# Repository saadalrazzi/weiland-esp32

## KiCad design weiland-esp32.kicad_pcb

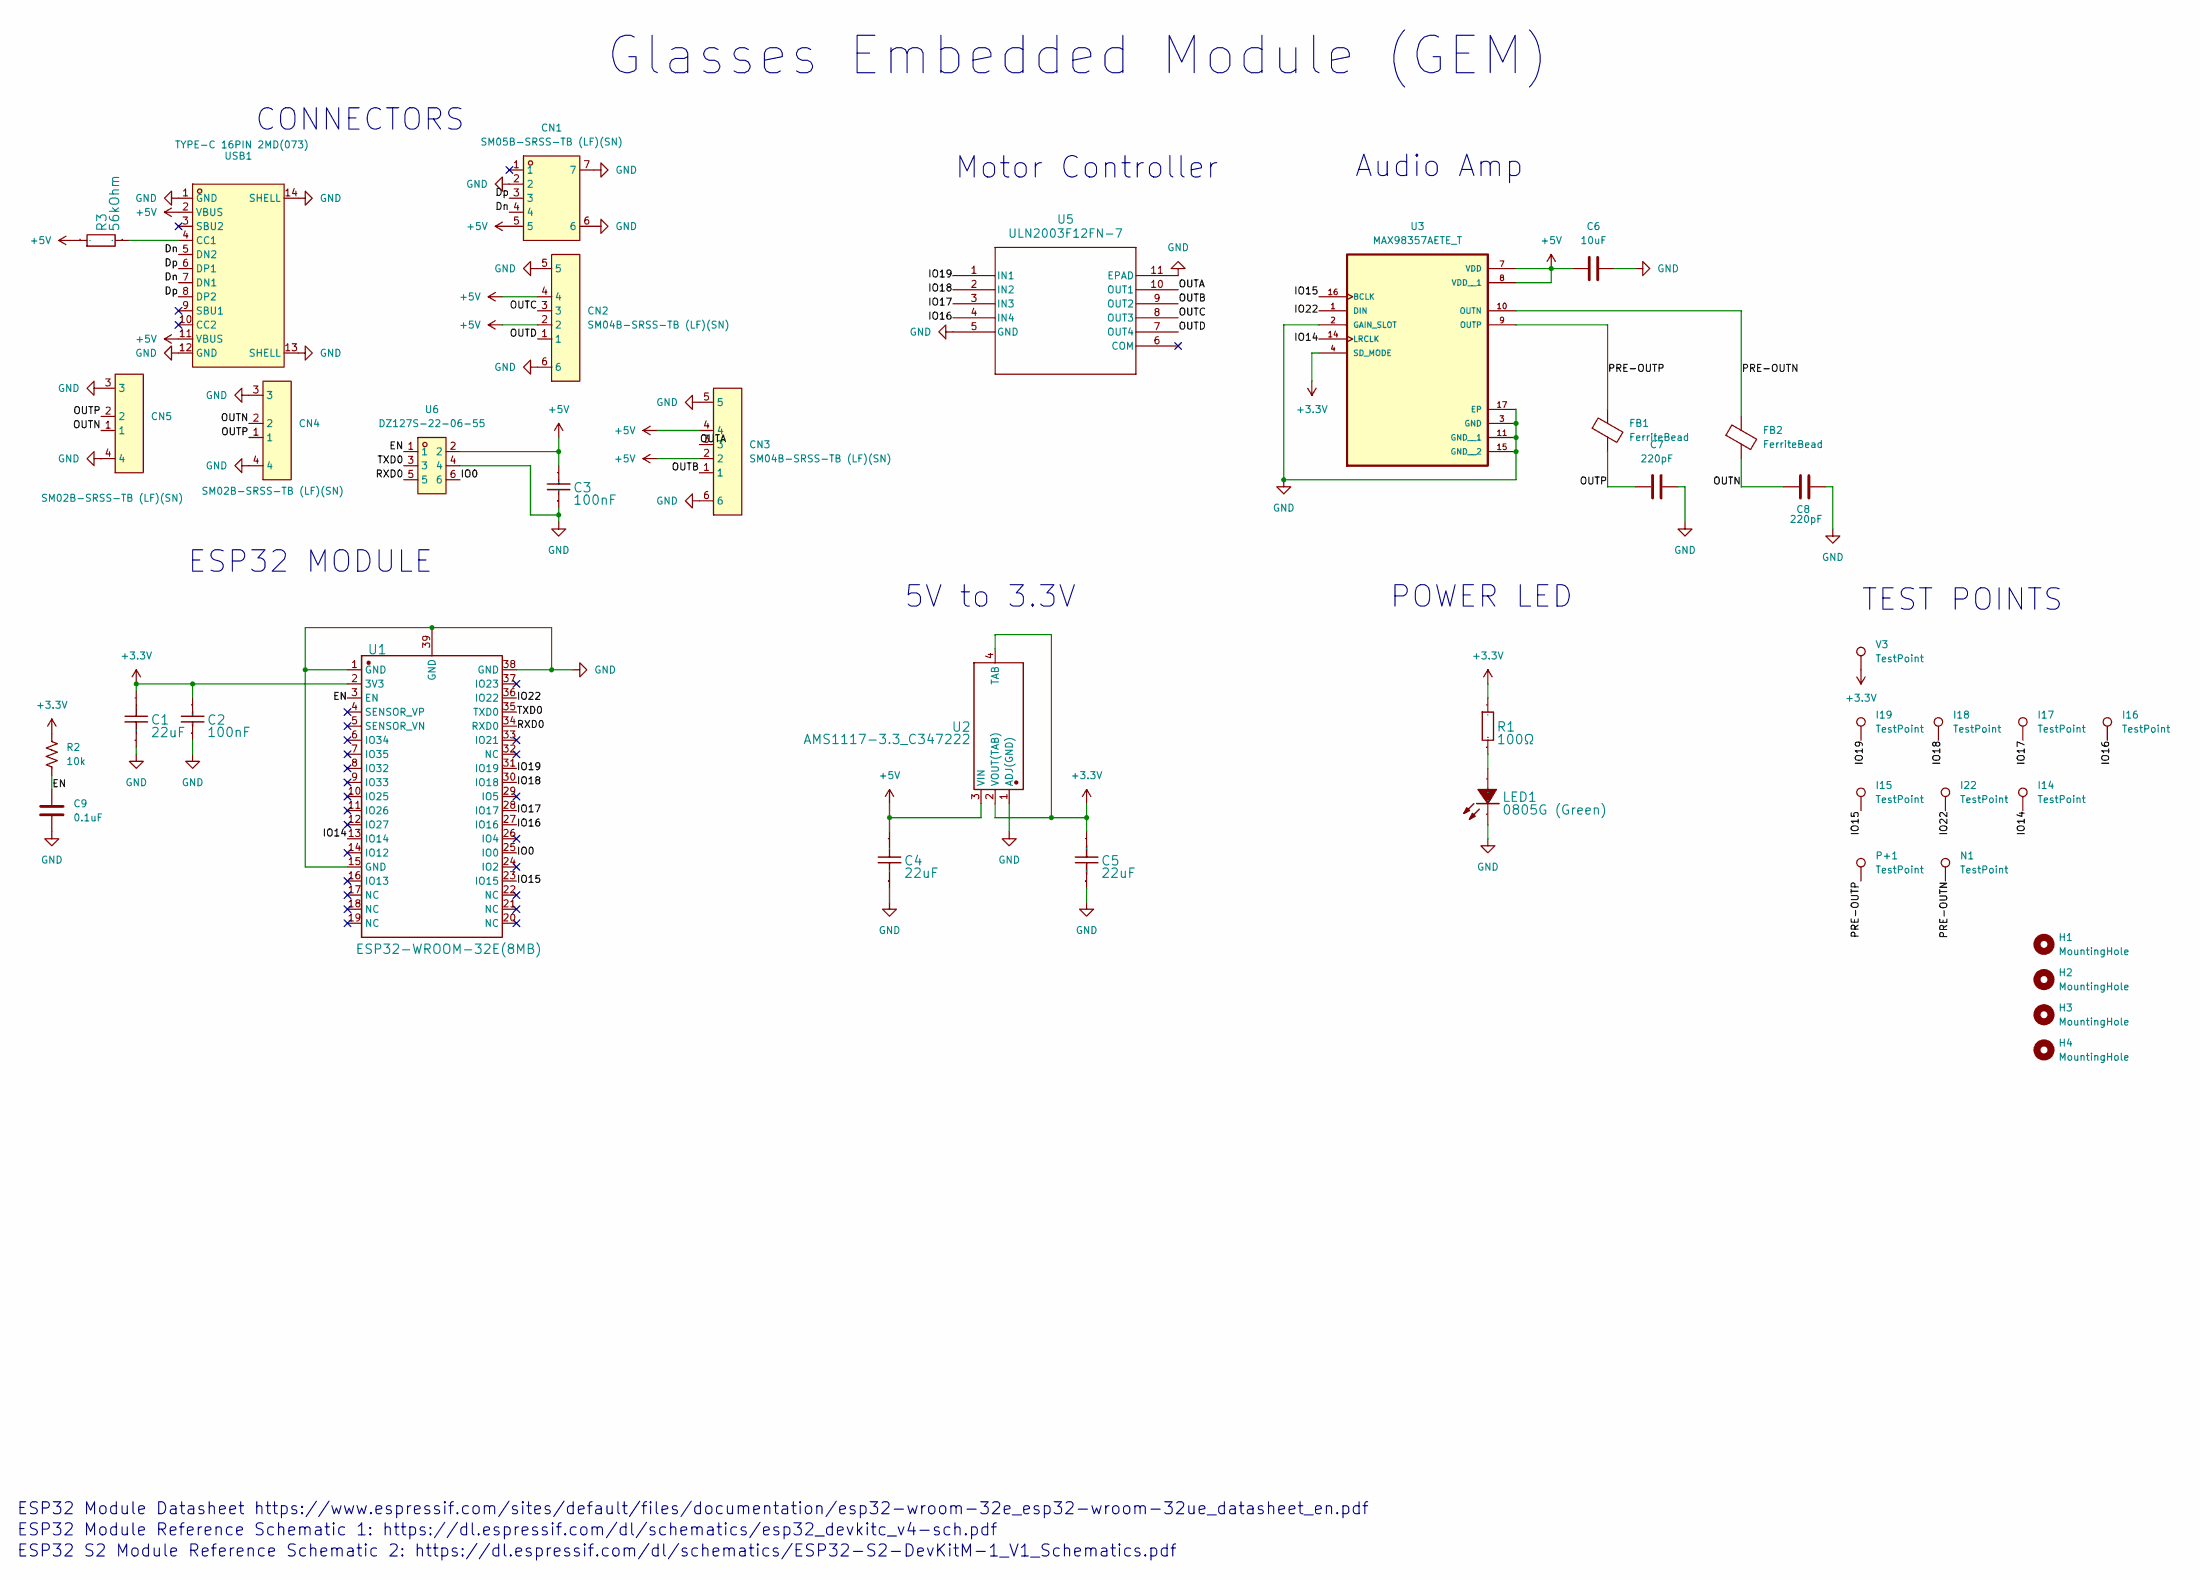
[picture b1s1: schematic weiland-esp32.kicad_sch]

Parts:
C1: 22uF; RESC1005X40N; Manufacturer Part CL21A226MAYNNNE
C2, C3: 100nF; CAPC1005X55N; Manufacturer Part CL05B104KO5NNNC
C4, C5: 22uF; RESC1005X40N; Manufacturer Part CL05A106MP5NUNC
C6: 10uF; RESC1005X40N
C7, C8: 220pF; RESC1005X40N
C9: 0.1uF; C_0402_1005Metric
CN1: SM05B-SRSS-TB (LF)(SN); CONN-SMD_SM05B-SRSS-TB-LF-SN; LCSC Part C136657
CN2, CN3: SM04B-SRSS-TB (LF)(SN); CONN-SMD_4P-P1.00_SM04B-SRSS-TB-LF-SN; LCSC Part C160404
CN4, CN5: SM02B-SRSS-TB (LF)(SN); CONN-SMD_2P-P1.00_SM02B-SRSS-TB-LF-SN; LCSC Part C160402
FB1, FB2: FerriteBead; 0402ferritebead
H1, H2, H3, H4: MountingHole; MountingHole_3.2mm_M3
I14, I15, I16, I17, I18, I19, I22: TestPoint; TestPoint_Pad_D1.0mm
LED1: 0805G (Green); LED_KP-1608SURCK; Manufacturer Part 0805G (Green)
N1: TestPoint; TestPoint_Pad_D1.0mm
P+1: TestPoint; TestPoint_Pad_D1.0mm
R1: 100Ω; RESC1005X40N; Manufacturer Part 0402WGF5101TCE
R2: 10k; R_0402_1005Metric
R3: 56kOhm; R_0402_1005Metric; Manufacturer Part 0402WGF5101TCE
U1: ESP32-WROOM-32E(8MB); ESP32-WROOM-32E; Manufacturer Part ESP32-WROOM-32E(8MB)
U2: AMS1117-3.3_C347222; SOT229P700X180-4N; Manufacturer Part AMS1117-3.3
U3: MAX98357AETE_T; QFN50P300X300X80-17N
U5: ULN2003F12FN-7; U-DFN3030-10_DIO
U6: DZ127S-22-06-55; HDR-SMD_6P-P1.27-V-M-R2-C3-S1.27-LS5.5-1; LCSC Part C5160759
USB1: TYPE-C 16PIN 2MD(073); USB-C-SMD_TYPE-C-6PIN-2MD-073; LCSC Part C2765186
V3: TestPoint; TestPoint_Pad_D1.0mm

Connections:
+3.3V: C1.2, C2.2, C5.2, R1.2, R2.1, U1.2 (3V3), U2.2 (VOUT(TAB)), U2.4 (TAB), U3.4 (SD_MODE), V3.1
+5V: C3.2, C4.2, C6.1, CN1.5, CN2.2, CN2.4, CN3.2, CN3.4, R3.2, U2.3 (VIN), U3.7 (VDD), U3.8 (VDD__1), U6.2, USB1.2 (VBUS), USB1.11 (VBUS)
/Dn: CN1.4, USB1.5 (DN2), USB1.7 (DN1)
/Dp: CN1.3, USB1.6 (DP1), USB1.8 (DP2)
/EN: C9.1, R2.2, U1.3 (EN), U6.1
/IO0: U1.25 (IO0), U6.6
/IO14: I14.1, U1.13 (IO14), U3.14 (LRCLK)
/IO15: I15.1, U1.23 (IO15), U3.16 (BCLK)
/IO16: I16.1, U1.27 (IO16), U5.4 (IN4)
/IO17: I17.1, U1.28 (IO17), U5.3 (IN3)
/IO18: I18.1, U1.30 (IO18), U5.2 (IN2)
/IO19: I19.1, U1.31 (IO19), U5.1 (IN1)
/IO22: I22.1, U1.36 (IO22), U3.1 (DIN)
/OUTA: CN3.3, U5.10 (OUT1)
/OUTB: CN3.1, U5.9 (OUT2)
/OUTC: CN2.3, U5.8 (OUT3)
/OUTD: CN2.1, U5.7 (OUT4)
/OUTN: C8.1, CN4.2, CN5.1, FB2.2
/OUTP: C7.1, CN4.1, CN5.2, FB1.2
/PRE-OUTN: FB2.1, N1.1, U3.10 (OUTN)
/PRE-OUTP: FB1.1, P+1.1, U3.9 (OUTP)
/RXD0: U1.34 (RXD0), U6.5
/TXD0: U1.35 (TXD0), U6.3
GND: C1.1, C2.1, C3.1, C4.1, C5.1, C6.2, C7.2, C8.2, C9.2, CN1.2, CN1.6, CN1.7, CN2.5, CN2.6, CN3.5, CN3.6, CN4.3, CN4.4, CN5.3, CN5.4, LED1.1 (K), U1.1 (GND), U1.15 (GND), U1.38 (GND), U1.39 (GND), U2.1 (ADJ(GND)), U3.2 (GAIN_SLOT), U3.3 (GND), U3.11 (GND__1), U3.15 (GND__2), U3.17 (EP), U5.5 (GND), U5.11 (EPAD), U6.4, USB1.1 (GND), USB1.12 (GND), USB1.13 (SHELL), USB1.14 (SHELL)
unnamed: LED1.2 (A), R1.1
unnamed: R3.1, USB1.4 (CC1)

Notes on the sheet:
POWER LED
Motor Controller
Glasses Embedded Module (GEM)
ESP32 Module Reference Schematic 1: https://dl.espressif.com/dl/schematics/esp32_devkitc_v4-sch.pdf
Audio Amp
TEST POINTS
ESP32 MODULE
CONNECTORS
ESP32 Module Datasheet https://www.espressif.com/sites/default/files/documentation/esp32-wroom-32e_esp32-wroom-32ue_datasheet_en.pdf
5V to 3.3V
ESP32 S2 Module Reference Schematic 2: https://dl.espressif.com/dl/schematics/ESP32-S2-DevKitM-1_V1_Schematics.pdf

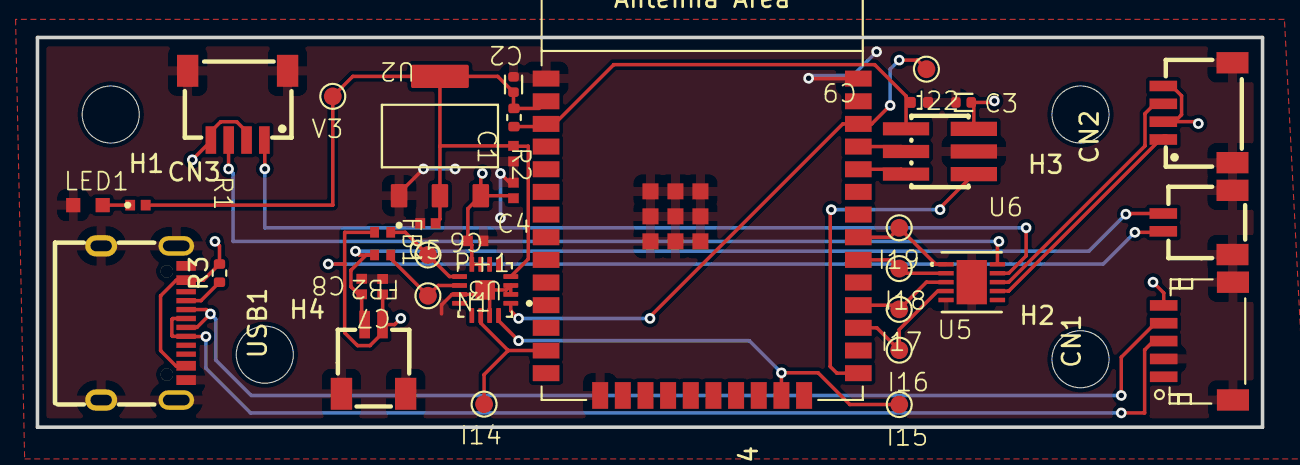
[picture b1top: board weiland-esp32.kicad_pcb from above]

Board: 2 copper layers, 68.7 x 21.8 mm, 40 parts (0 on the bottom side), 26 nets.

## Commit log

2025-01-17 antenna can't be on the board itself (interference)
2025-02-04 routing draft completed
2025-02-28 last commit before 4 motor branch
2025-03-14 jst connectors
2025-04-04 good schematic before unshrouded header
2025-04-11 test point schematic, before adding to layout
2025-04-18 52x39 board w/ holes
2025-04-18 before deleting all traces
2025-05-06 board complete
2025-05-06 latest
2025-05-07 test
2025-05-30 working board but wrong placement of holes
2025-05-30 fully routed board
